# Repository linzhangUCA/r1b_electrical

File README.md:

# r1b_electrical

## Schematic

## Assembled Example

## Errata

## Parts List

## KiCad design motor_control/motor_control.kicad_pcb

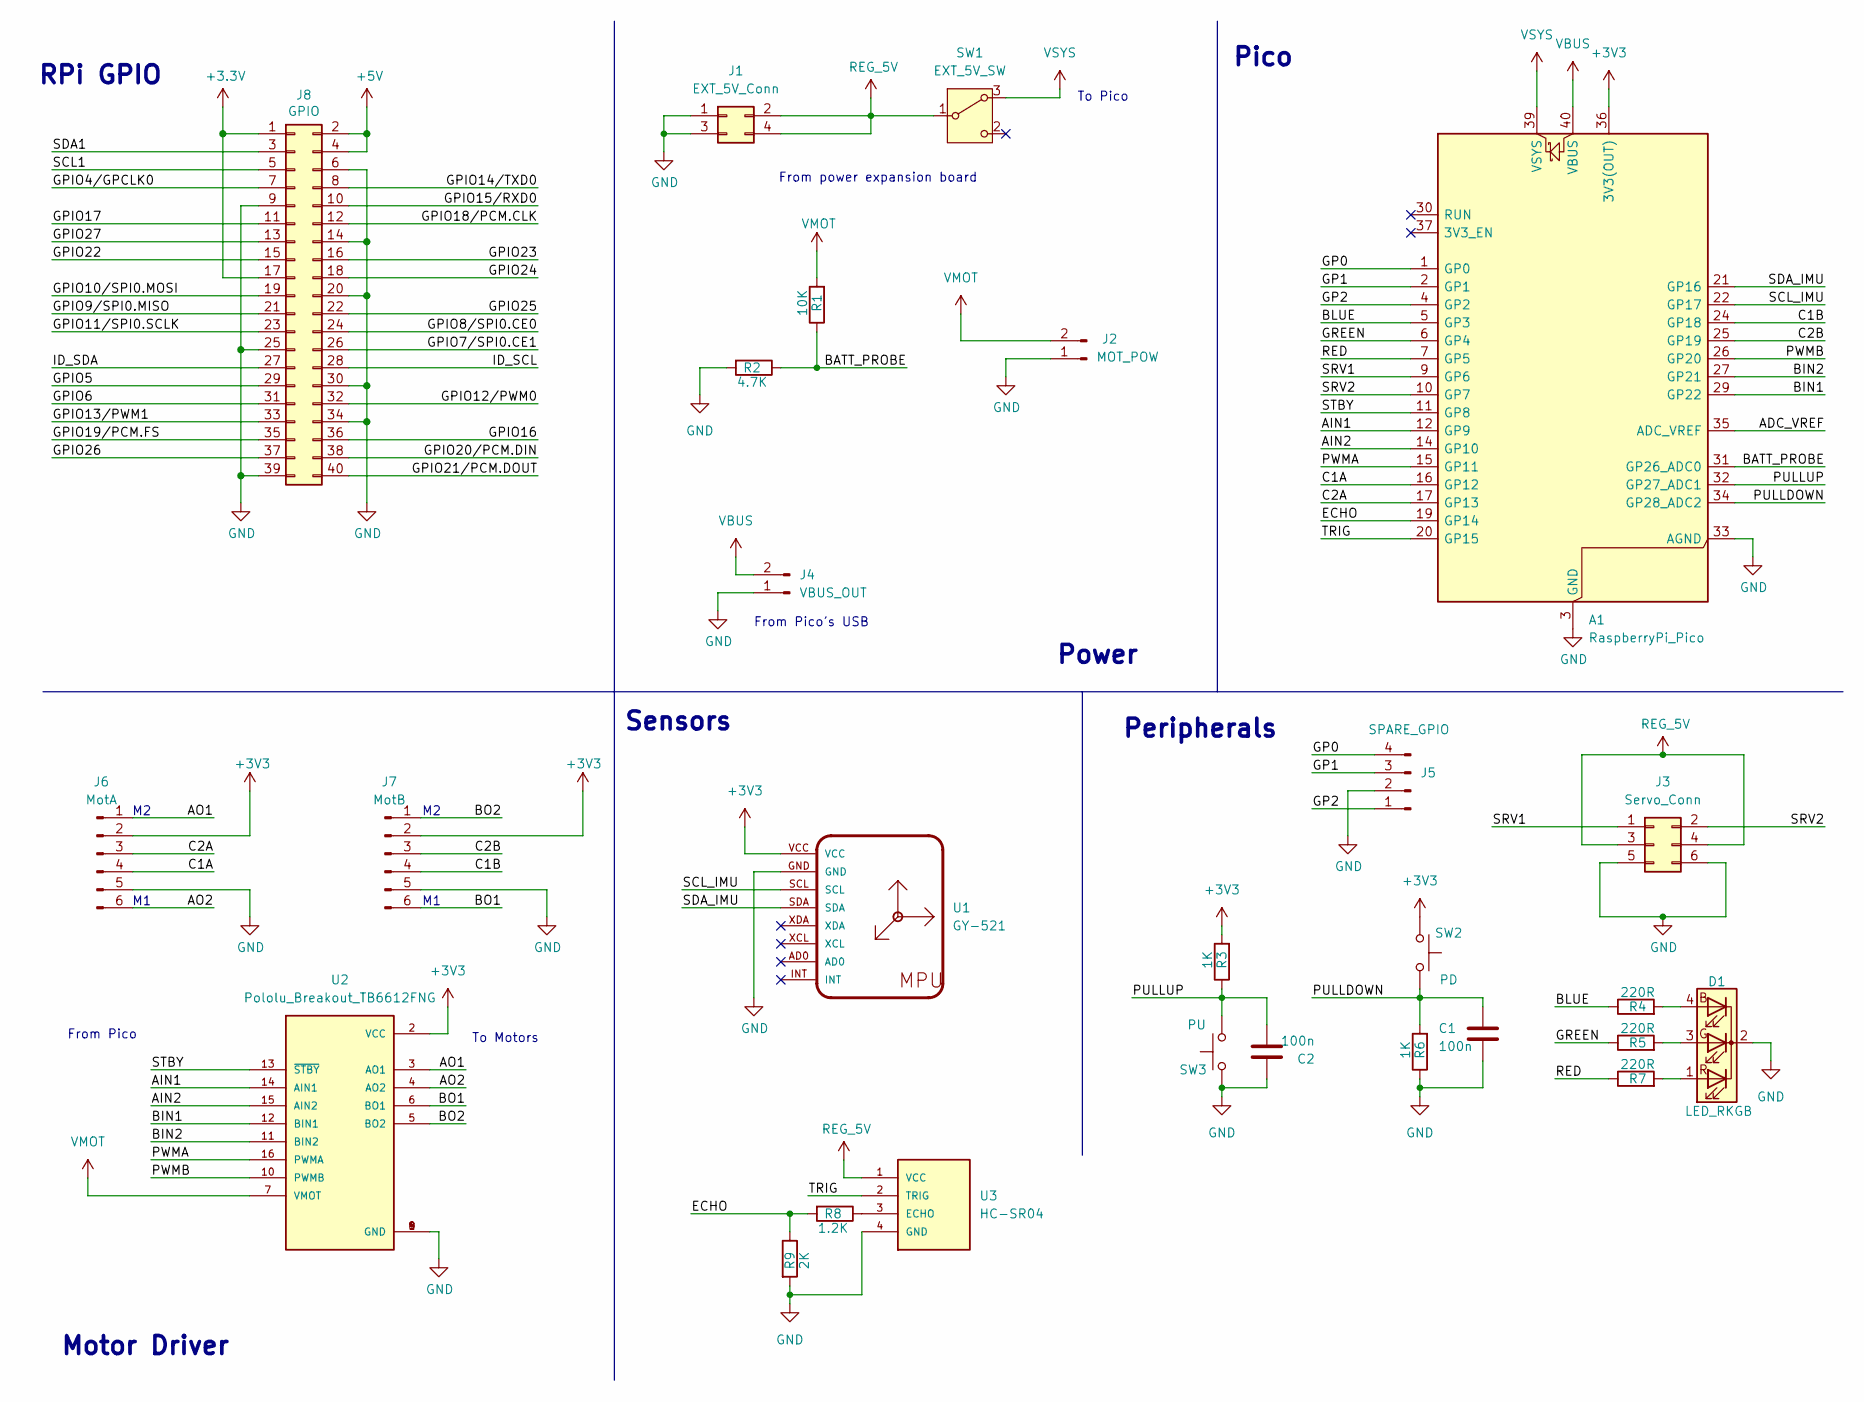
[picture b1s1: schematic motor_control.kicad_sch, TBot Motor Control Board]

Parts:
A1: RaspberryPi_Pico; RaspberryPi_Pico_Common_THT
C1, C2: 100n; C_Disc_D4.7mm_W2.5mm_P5.00mm
D1: LED_RKGB; LED_D5.0mm-4_RGB_Wide_Pins
J1: EXT_5V_Conn; PinHeader_2x02_P2.54mm_Vertical
J2: MOT_POW; JST_XH_S2B-XH-A_1x02_P2.50mm_Horizontal
J3: Servo_Conn; PinHeader_2x03_P2.54mm_Vertical
J4: VBUS_OUT; PinHeader_1x02_P2.54mm_Vertical
J5: SPARE_GPIO; PinHeader_1x04_P2.54mm_Vertical
J6: MotA; PinHeader_1x06_P2.54mm_Vertical
J7: MotB; PinHeader_1x06_P2.54mm_Vertical
J8: GPIO; PinSocket_2x20_P2.54mm_Vertical
R1: 10K; R_Axial_DIN0207_L6.3mm_D2.5mm_P7.62mm_Horizontal
R2: 4.7K; R_Axial_DIN0207_L6.3mm_D2.5mm_P7.62mm_Horizontal
R3, R6: 1K; R_Axial_DIN0207_L6.3mm_D2.5mm_P7.62mm_Horizontal
R4, R5, R7: 220R; R_Axial_DIN0207_L6.3mm_D2.5mm_P7.62mm_Horizontal
R8: 1.2K; R_Axial_DIN0207_L6.3mm_D2.5mm_P7.62mm_Horizontal
R9: 2K; R_Axial_DIN0207_L6.3mm_D2.5mm_P7.62mm_Horizontal
SW1: EXT_5V_SW; SW_Slide-03_Wuerth-WS-SLTV_10x2.5x6.4_P2.54mm
SW2: PD; SW_PUSH_6mm
SW3: PU; SW_PUSH_6mm
U1: GY-521
U2: Pololu_Breakout_TB6612FNG; SHIELD_POLOLU-713
U3: HC-SR04; XCVR_HC-SR04

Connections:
+3.3V: J8.1, J8.17
+3V3: A1.36 (3V3(OUT)), J6.2, J7.2, R3.2, SW2.1, U1.VCC, U2.2 (VCC)
+5V: J8.2, J8.4
/ADC_VREF: A1.35 (ADC_VREF)
/AIN1: A1.12 (GP9), U2.14 (AIN1)
/AIN2: A1.14 (GP10), U2.15 (AIN2)
/AO1: J6.1, U2.3 (AO1)
/AO2: J6.6, U2.4 (AO2)
/BATT_PROBE: A1.31 (GP26_ADC0), R1.1, R2.1
/BIN1: A1.29 (GP22), U2.12 (BIN1)
/BIN2: A1.27 (GP21), U2.11 (BIN2)
/BLUE: A1.5 (GP3), R4.1
/BO1: J7.6, U2.6 (BO1)
/BO2: J7.1, U2.5 (BO2)
/C1A: A1.16 (GP12), J6.4
/C1B: A1.24 (GP18), J7.4
/C2A: A1.17 (GP13), J6.3
/C2B: A1.25 (GP19), J7.3
/ECHO: A1.19 (GP14), R8.2, R9.1
/GP0: A1.1 (GP0), J5.4
/GP1: A1.2 (GP1), J5.3
/GP2: A1.4 (GP2), J5.1
/GPIO4/GPCLK0: J8.7
/GPIO5: J8.29
/GPIO6: J8.31
/GPIO7/SPI0.CE1: J8.26
/GPIO8/SPI0.CE0: J8.24
/GPIO9/SPI0.MISO: J8.21
/GPIO10/SPI0.MOSI: J8.19
/GPIO11/SPI0.SCLK: J8.23
/GPIO12/PWM0: J8.32
/GPIO13/PWM1: J8.33
/GPIO14/TXD0: J8.8
/GPIO15/RXD0: J8.10
/GPIO16: J8.36
/GPIO17: J8.11
/GPIO18/PCM.CLK: J8.12
/GPIO19/PCM.FS: J8.35
/GPIO20/PCM.DIN: J8.38
/GPIO21/PCM.DOUT: J8.40
/GPIO22: J8.15
/GPIO23: J8.16
/GPIO24: J8.18
/GPIO25: J8.22
/GPIO26: J8.37
/GPIO27: J8.13
/GREEN: A1.6 (GP4), R5.1
/ID_SCL: J8.28
/ID_SDA: J8.27
/PULLDOWN: A1.34 (GP28_ADC2), C1.2, R6.2, SW2.2
/PULLUP: A1.32 (GP27_ADC1), C2.1, R3.1, SW3.2
/PWMA: A1.15 (GP11), U2.16 (PWMA)
/PWMB: A1.26 (GP20), U2.10 (PWMB)
/RED: A1.7 (GP5), R7.1
/SCL1: J8.5
/SCL_IMU: A1.22 (GP17), U1.SCL
/SDA1: J8.3
/SDA_IMU: A1.21 (GP16), U1.SDA
/SRV1: A1.9 (GP6), J3.1
/SRV2: A1.10 (GP7), J3.2
/STBY: A1.11 (GP8), U2.13 (~STBY)
/TRIG: A1.20 (GP15), U3.2 (TRIG)
GND: A1.3 (GND), A1.8 (GND), A1.13 (GND), A1.18 (GND), A1.23 (GND), A1.28 (GND), A1.33 (AGND), A1.38 (GND), C1.1, C2.2, D1.2 (K), J1.1, J1.3, J2.1, J3.5, J3.6, J4.1, J5.2, J6.5, J7.5, J8.6, J8.9, J8.14, J8.20, J8.25, J8.30, J8.34, J8.39, R2.2, R6.1, R9.2, SW3.1, U1.GND, U2.1 (GND), U2.8 (GND), U2.9 (GND), U3.4 (GND)
unnamed: D1.4 (BA), R4.2
unnamed: D1.3 (GA), R5.2
unnamed: D1.1 (RA), R7.2
unnamed: R8.1, U3.3 (ECHO)
REG_5V: J1.2, J1.4, J3.3, J3.4, SW1.1 (B), U3.1 (VCC)
VBUS: A1.40 (VBUS), J4.2
VMOT: J2.2, R1.2, U2.7 (VMOT)
VSYS: A1.39 (VSYS), SW1.3 (A)

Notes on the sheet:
Pico
From power expansion board
From Pico's USB
Sensors
To Motors
Peripherals
From Pico
Motor Driver
To Pico
Power
RPi GPIO

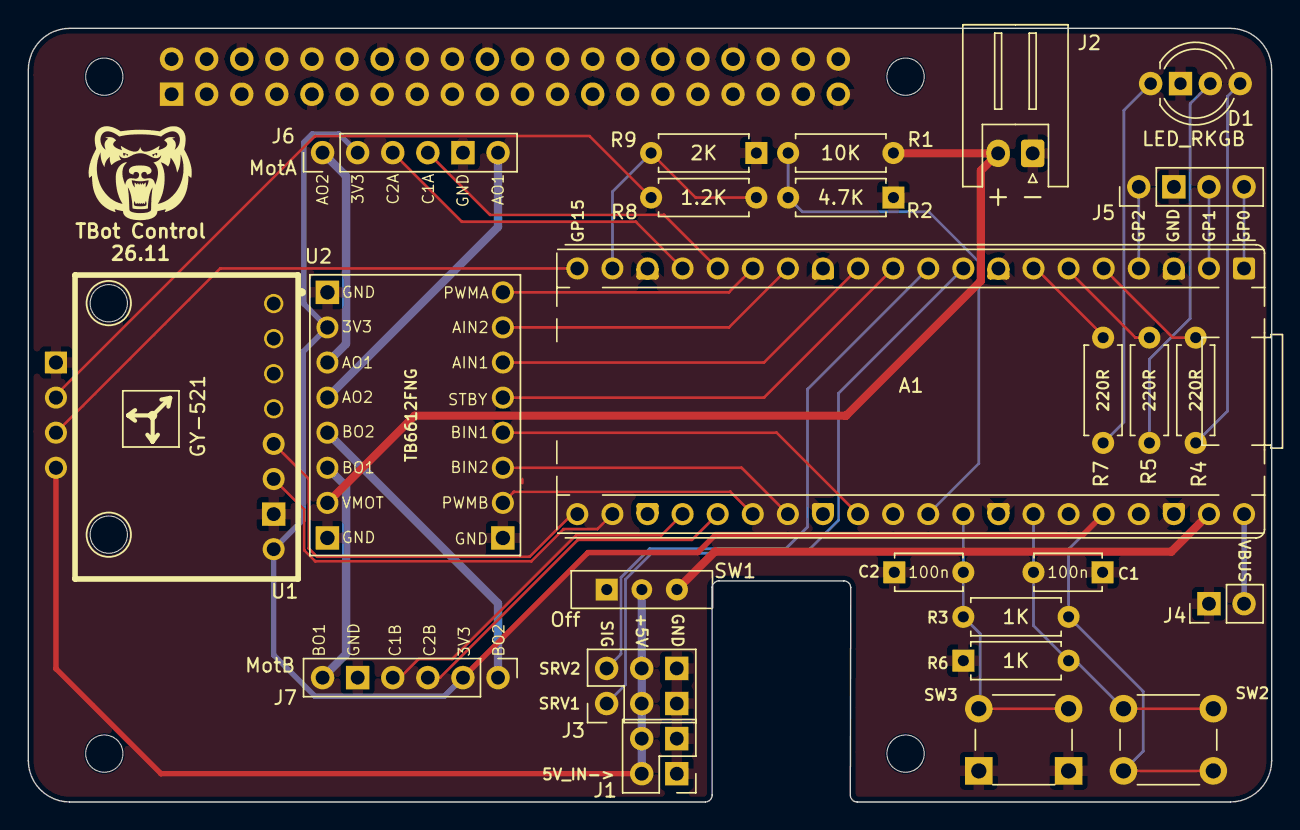
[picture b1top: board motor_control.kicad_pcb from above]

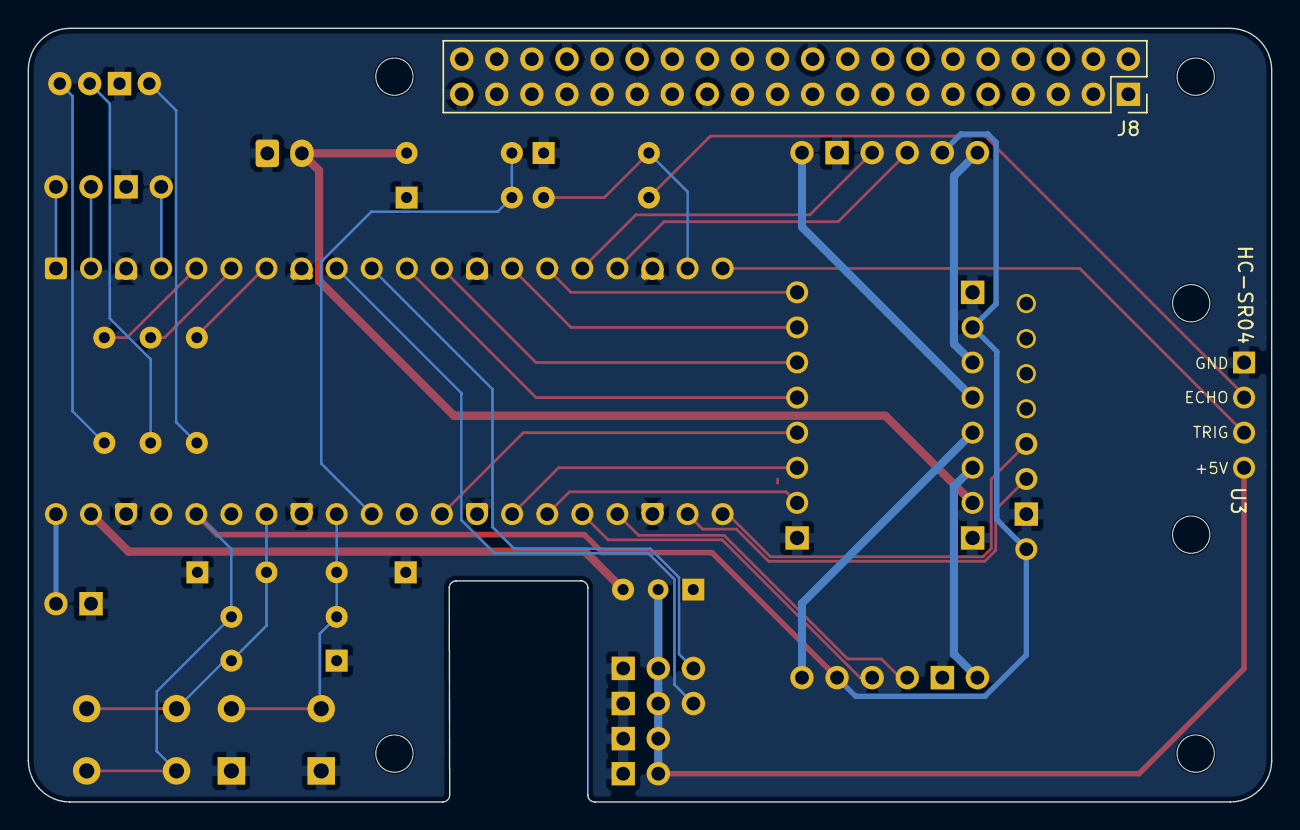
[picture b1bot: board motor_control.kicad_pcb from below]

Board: 4 copper layers, 90.0 x 56.0 mm, 31 parts (2 on the bottom side), 42 nets.

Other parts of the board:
MH1, MH2, MH3, MH4: MountingHole_2.7mm_M2.5

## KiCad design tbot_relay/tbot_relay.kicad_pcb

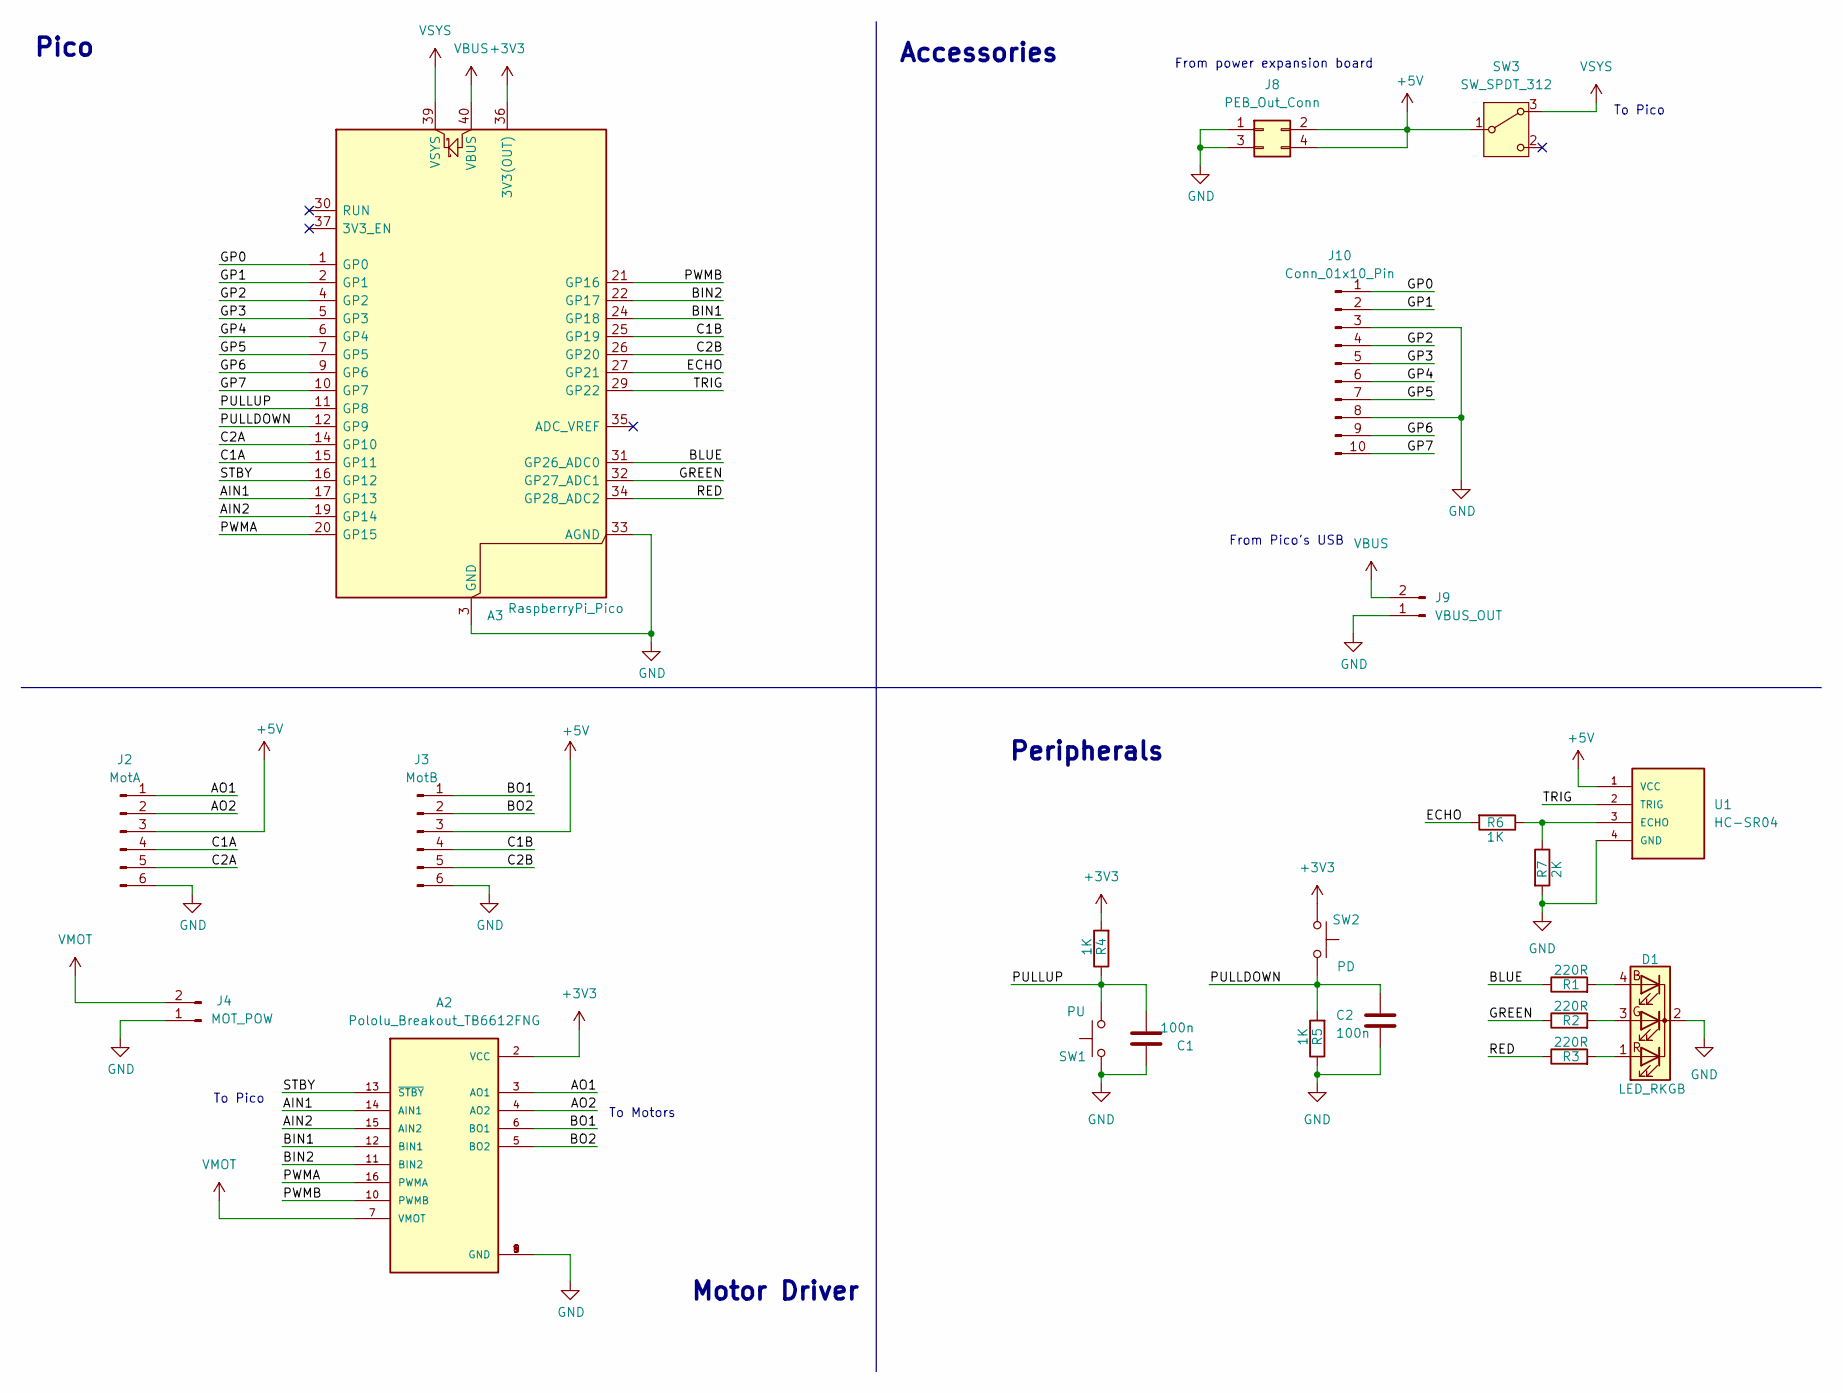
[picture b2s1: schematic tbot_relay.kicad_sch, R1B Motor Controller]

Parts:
A2: Pololu_Breakout_TB6612FNG; SHIELD_POLOLU-713
A3: RaspberryPi_Pico; RaspberryPi_Pico_Common_Unspecified
C1, C2: 100n; C_Disc_D4.7mm_W2.5mm_P5.00mm
D1: LED_RKGB; LED_D5.0mm-4_RGB_Wide_Pins
J2: MotA; PinHeader_1x06_P2.54mm_Vertical
J3: MotB; PinHeader_1x06_P2.54mm_Vertical
J4: MOT_POW; JST_XH_B2B-XH-A_1x02_P2.50mm_Vertical
J8: PEB_Out_Conn; PinHeader_2x02_P2.54mm_Vertical
J9: VBUS_OUT; PinHeader_1x02_P2.54mm_Vertical
J10: Conn_01x10_Pin; PinHeader_1x10_P2.54mm_Vertical
R1, R2, R3: 220R; R_Axial_DIN0207_L6.3mm_D2.5mm_P7.62mm_Horizontal
R4, R5, R6: 1K; R_Axial_DIN0207_L6.3mm_D2.5mm_P7.62mm_Horizontal
R7: 2K; R_Axial_DIN0207_L6.3mm_D2.5mm_P7.62mm_Horizontal
SW1: PU; SW_PUSH_6mm
SW2: PD; SW_PUSH_6mm
SW3: SW_SPDT_312; SW_Slide-03_Wuerth-WS-SLTV_10x2.5x6.4_P2.54mm
U1: HC-SR04; XCVR_HC-SR04

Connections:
+3V3: A2.2 (VCC), A3.36 (3V3(OUT)), R4.2, SW2.1
+5V: J2.3, J3.3, J8.2, J8.4, SW3.1 (B), U1.1 (VCC)
/AIN1: A2.14 (AIN1), A3.17 (GP13)
/AIN2: A2.15 (AIN2), A3.19 (GP14)
/AO1: A2.3 (AO1), J2.1
/AO2: A2.4 (AO2), J2.2
/BIN1: A2.12 (BIN1), A3.24 (GP18)
/BIN2: A2.11 (BIN2), A3.22 (GP17)
/BLUE: A3.31 (GP26_ADC0), R1.1
/BO1: A2.6 (BO1), J3.1
/BO2: A2.5 (BO2), J3.2
/C1A: A3.15 (GP11), J2.4
/C1B: A3.25 (GP19), J3.4
/C2A: A3.14 (GP10), J2.5
/C2B: A3.26 (GP20), J3.5
/ECHO: A3.27 (GP21), R6.2
/GP0: A3.1 (GP0), J10.1
/GP1: A3.2 (GP1), J10.2
/GP2: A3.4 (GP2), J10.4
/GP3: A3.5 (GP3), J10.5
/GP4: A3.6 (GP4), J10.6
/GP5: A3.7 (GP5), J10.7
/GP6: A3.9 (GP6), J10.9
/GP7: A3.10 (GP7), J10.10
/GREEN: A3.32 (GP27_ADC1), R2.1
/PULLDOWN: A3.12 (GP9), C2.2, R5.2, SW2.2
/PULLUP: A3.11 (GP8), C1.1, R4.1, SW1.2
/PWMA: A2.16 (PWMA), A3.20 (GP15)
/PWMB: A2.10 (PWMB), A3.21 (GP16)
/RED: A3.34 (GP28_ADC2), R3.1
/STBY: A2.13 (~STBY), A3.16 (GP12)
/TRIG: A3.29 (GP22), U1.2 (TRIG)
GND: A2.1 (GND), A2.8 (GND), A2.9 (GND), A3.3 (GND), A3.8 (GND), A3.13 (GND), A3.18 (GND), A3.23 (GND), A3.28 (GND), A3.33 (AGND), A3.38 (GND), C1.2, C2.1, D1.2 (K), J2.6, J3.6, J4.1, J8.1, J8.3, J9.1, J10.3, J10.8, R5.1, R7.2, SW1.1, U1.4 (GND)
unnamed: D1.4 (BA), R1.2
unnamed: D1.3 (GA), R2.2
unnamed: D1.1 (RA), R3.2
unnamed: R6.1, R7.1, U1.3 (ECHO)
VBUS: A3.40 (VBUS), J9.2
VMOT: A2.7 (VMOT), J4.2
VSYS: A3.39 (VSYS), SW3.3 (A)

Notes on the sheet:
Pico
From power expansion board
From Pico's USB
To Motors
Peripherals
To Pico
Motor Driver
Accessories

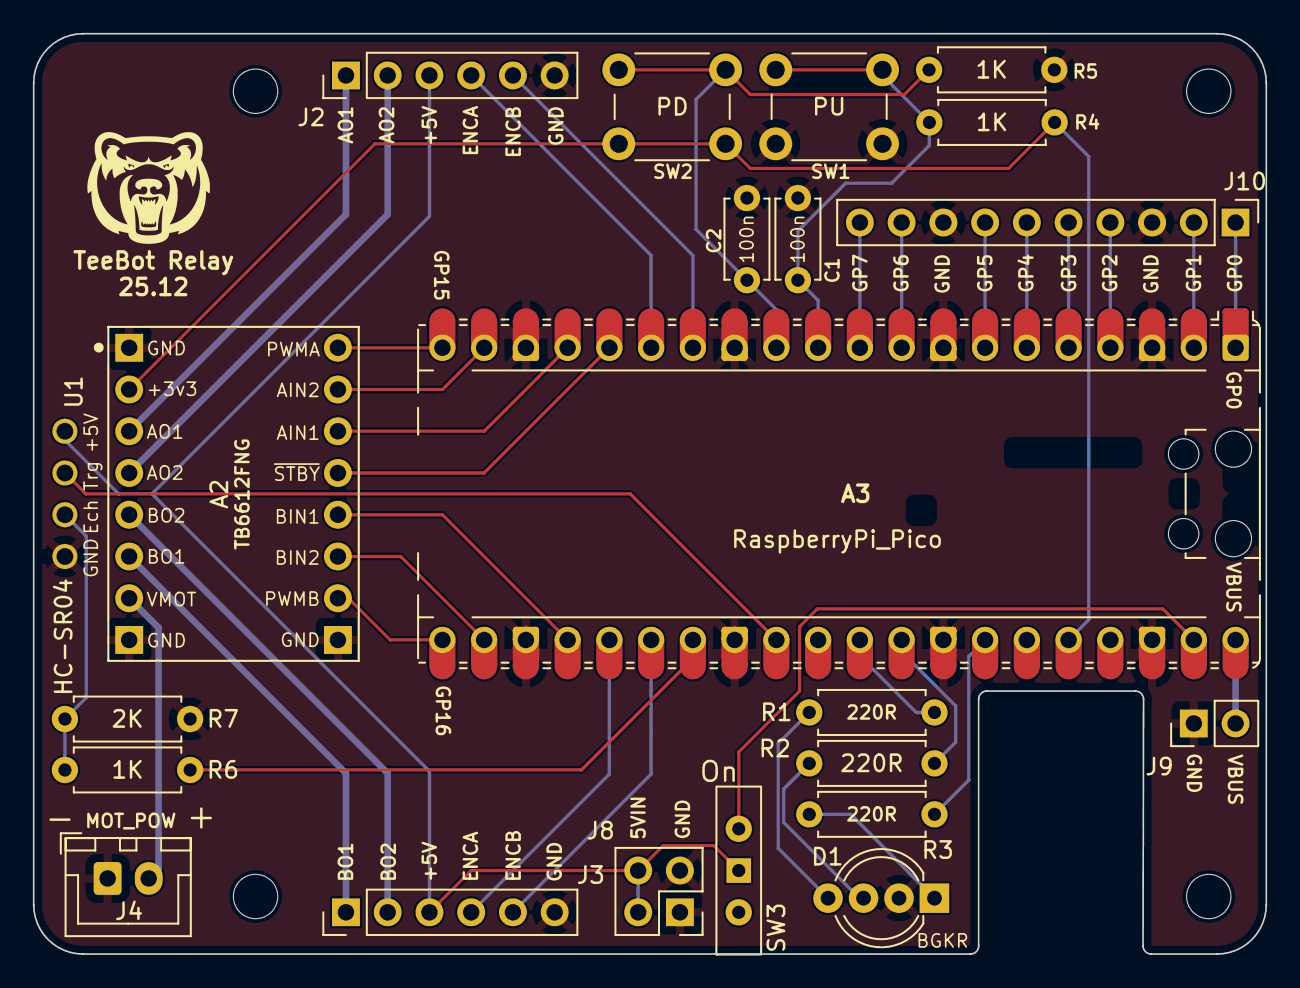
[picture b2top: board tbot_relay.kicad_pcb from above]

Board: 4 copper layers, 75.0 x 56.0 mm, 26 parts (0 on the bottom side), 40 nets.

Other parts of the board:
MH1, MH2, MH3, MH4: MountingHole_2.7mm_M2.5

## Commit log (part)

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2025-07-20 create KiCAD project
2025-07-20 add common cathod RGB LED to schematic
2025-07-20 add buttons and debounce circuits
2025-07-20 use net labels
2025-07-21 update schematic with ultrasound sensor
2025-07-21 add custom HC-SR04 symbol and footprint to project
2025-07-22 upload tb6612 breakout board library
2025-07-22 add motor driver and connectors
2025-07-24 replace switch with a jumper
2025-07-24 replace tb6612 power switch with a 01x02 pin header
2025-07-24 add comm connections between pi and pico
2025-07-29 finish up schematic
2025-07-31 assign footprints to capacitors
2025-07-31 assign footprints to resistors
2025-08-01 assign footprints to more parts
2025-08-01 assign all footprints
2025-08-13 update board setup and edge cuts
2025-08-13 update pico footprint
2025-08-13 layout v1
2025-08-14 wiring v1
2025-08-14 add 3d model for hcsr04
2025-08-14 update 3d model for hcsr04
2025-08-14 update tb6612 3d model
2025-08-14 update pico 3d model
2025-08-14 add bear head logo
2025-08-14 adjust labels
2025-08-16 final tweak pcb
2025-08-16 export gerber
2025-08-31 plot schematic
2025-09-06 fix hcsr04 voltage divider
2025-09-13 update schematic and pcb
    1. added a input 01x02 header for PEB power up +5V
    2. switched to +5V to power up sonar and encoders
    3. set jumper between +5V and PEB 5V input
    4. upgraded motor driver input to JST-XH
    5. updated footprints
2025-09-13 update schematic text labels
2025-10-23 update pull-down debouncer
2025-10-23 update REG_5V as source for all 5V components
2025-10-23 update unused GP pins net labels
2025-10-23 relabeling motor control wires
2025-10-24 rearange gp pins
2025-10-24 rearrange gp0 to gp7 connections
2025-10-24 assign footprint to connectors
2025-10-24 fix j9 footprint and update pcb
2025-10-24 update motor connector pins
2025-10-24 update layout
2025-10-24 minor update layout
2025-10-24 update wiring
2025-10-24 fix drc issues
2025-10-25 generate jlcpcb gerber
2025-10-25 update schematic pdf
2025-10-26 export board step
2025-11-16 upload an example
2025-11-16 add schematic image
2025-11-16 reserve parts list
2025-11-24 fix motor driver labels
2025-11-24 add motor driver errata
2025-12-22 update r1b design to tbot
2025-12-22 remove old gerbers
2025-12-22 remove old design
2025-12-22 save final changes
